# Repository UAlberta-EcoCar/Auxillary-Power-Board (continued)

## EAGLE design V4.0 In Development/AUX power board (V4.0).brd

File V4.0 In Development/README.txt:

Changes From V3

Completed:
	SEPTIC 12V 1.25A Surface Mount Regulator w/ Vin 8-18V, 90% efficiency

	Surface Mount 328p

	A -12V low current regulator for operation of op-amps.

	Surface Mount 5V 1.25A (it does 2A) buck convertor. 

	Using a cheaper inductor for the 5V regulator

	Using low side nMOS for reverse polarity protection

	Only have 2 outputs. One to FCC board (if needed) and to Aux Board. Still keep 
	a header for testing.

	I inverted the RJ11 Port

	Implemented Overvoltage protection
	
	Implemented reverse voltage protection
	
	Add a standardized fuse holder

Planned:
	i2c 0.96" 128x64 display (Possibly a no to data logging, favoring real-time power measurements)

	Use existing Heat Sink and place on the bottom of the board

	Add holes to the outside of the board (ease of mounting)

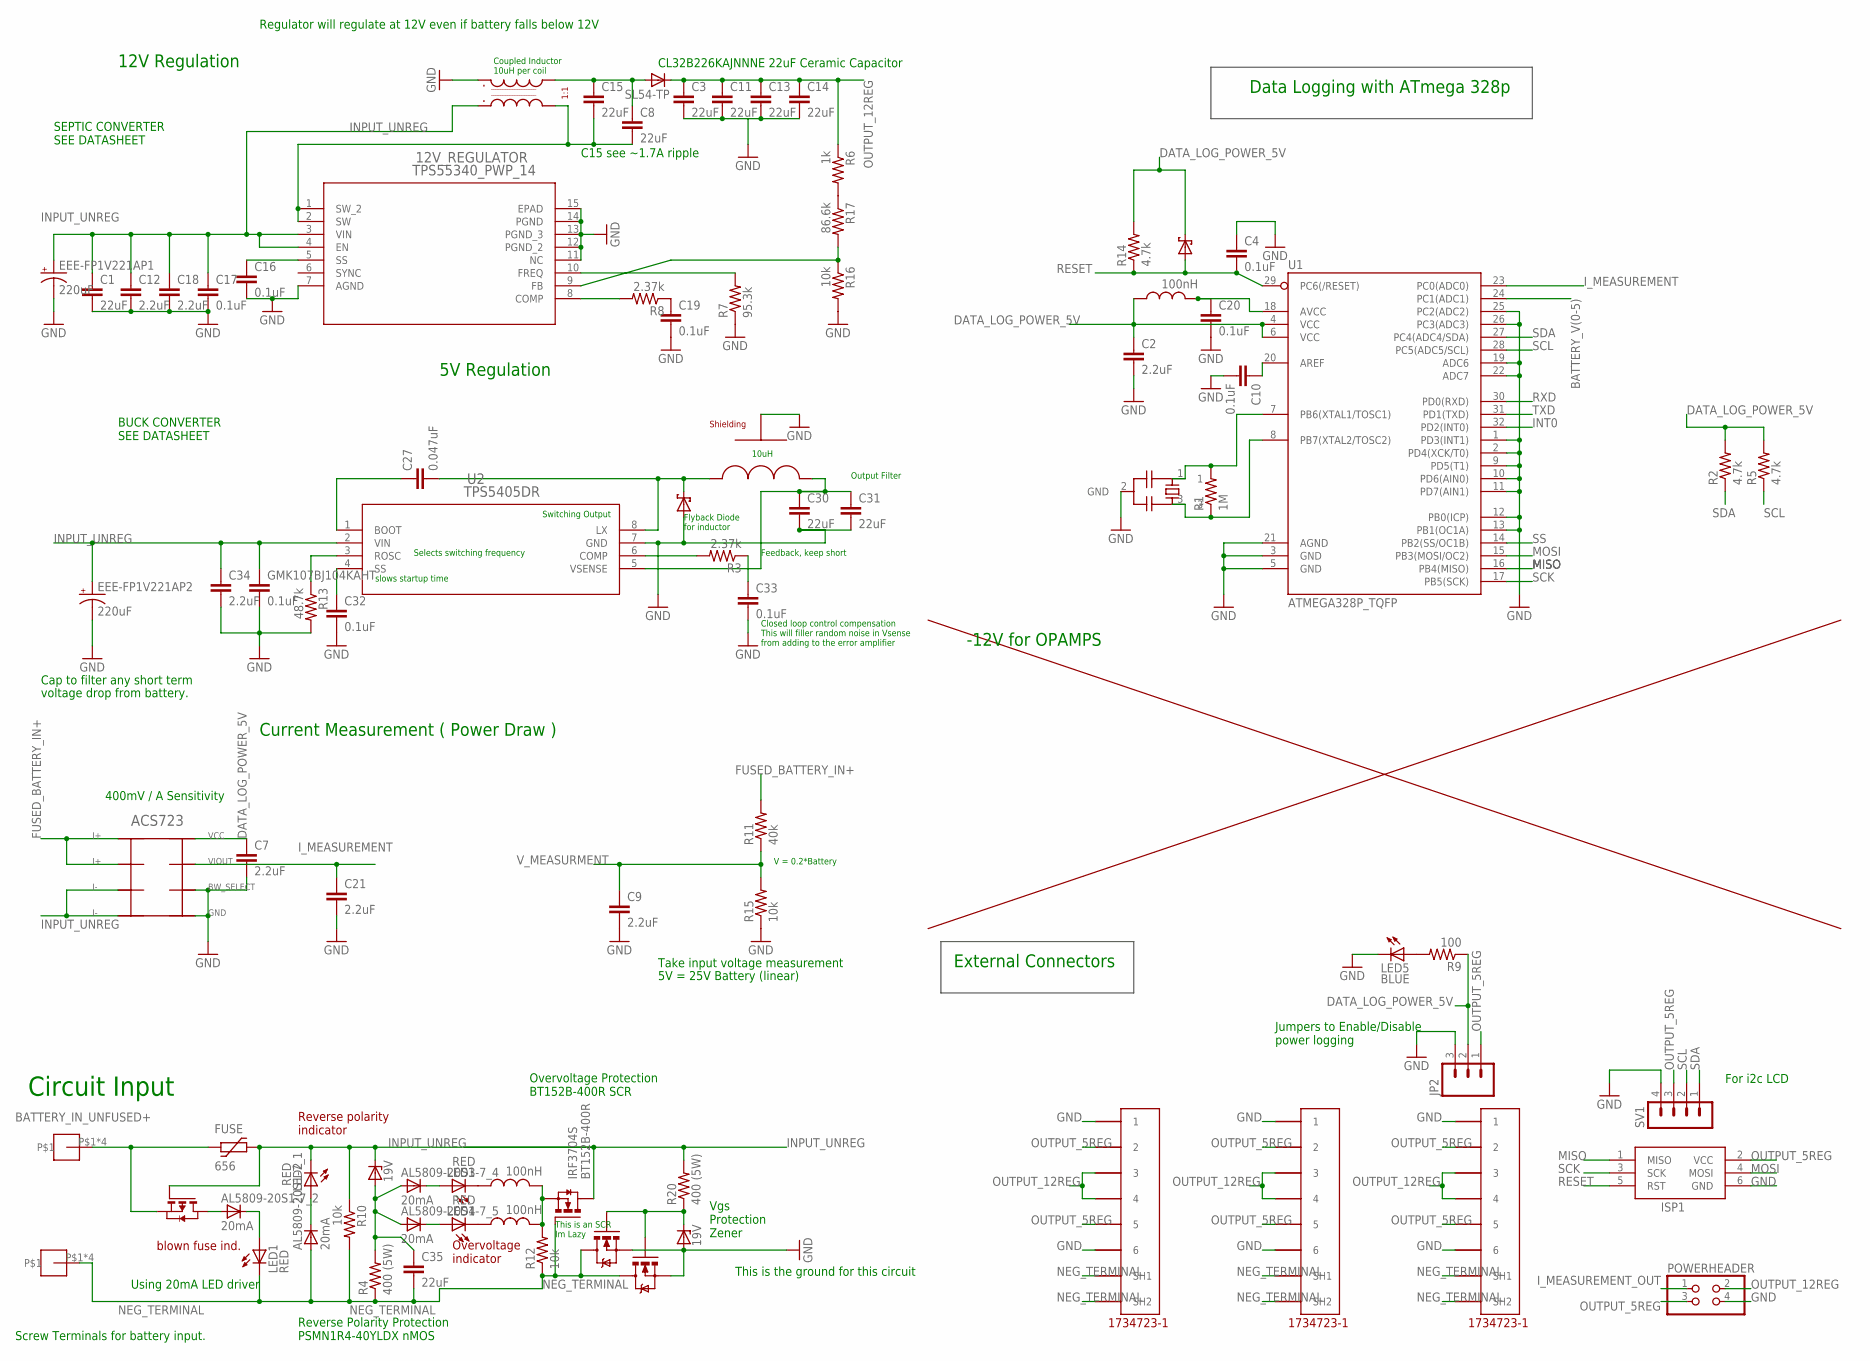
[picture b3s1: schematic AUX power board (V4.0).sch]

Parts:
1N5354BRLG, 1N5356BRLG_1: 19V; DO41Z10
12V_REGULATOR: TPS55340_PWP_14; PWP14
16MHZ: CSTCE16M0V53-R0; RESONATOR
AL5809-20S1-7_1, AL5809-20S1-7_2, AL5809-20S1-7_4, AL5809-20S1-7_5: 20mA; SOD123
BT152B-400R: IRF3704S; D2PACK
C1, C3, C8, C11, C13, C14, C15, C30, C31, C35: 22uF; C1210
C2, C7, C9, C12, C18, C21, C34: 2.2uF; C0603
C4, C10, C16, C17, C19, C20, C32, C33: 0.1uF; C0603
C27: 0.047uF; C0603
EEE-FP1V221AP1, EEE-FP1V221AP2: 220uF; 175TMP-0808
FUSE: 656
GMK107BJ104KAHT: 0.1uF; C0603
ISP1: AVRISP-6; AVRISP
JP2: M03PTH; 1X03
LED1, LED2, LED3, LED4: RED; SML1206
LED5: BLUE; SML1206
MLZ2012DR10DT000, MLZ2012DR10DT001, MLZ2012DR10DT002: 100nH; L2012C
MURS120T3G, MURS120T3G1: MBRS130LT3; SMB
POWERHEADER: PINHD-2X2; 2X02
PSMN1R4-40YLDX1, PSMN1R4-40YLDX2: MOSFET-NCHANNELFDS6630A; POWERSO08
R1: 1M; R0603
R2, R5, R14: 4.7k; R0805
R3, R8: 2.37k; R0603
R4, R20: 400 (5W); P0817/22
R6: 1k; R0805
R7: 95.3k; R0603
R9: 100; R0805
R10, R12, R15, R16: 10k; R0805
R11: 40k; R0805
R13: 48.7k; R0805
R17: 86.6k; R0805
SL54-TP: DIODE_E-SMC; DIODE_SMC
SV1: MA04-1
U1: ATMEGA328P_TQFP; TQFP32-08
U2: TPS5405DR; D8
U$1: ACS723; SO08
U$3, U$4, U$10: 5555140-6; 1734723-1_RJ11
U$5: CDEP147NP-100MC-125; NONSTANDARD
U$6, U$7: SCREW-8191
U$9: 744873100; 1592
ZVP4525E6TA_1: MOSFET-PCHANNELFDS6675; SOT23-6

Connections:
BATTERY_IN_UNFUSED+: FUSE.P$1 (1), U$6.P$1, U$6.P$2, U$6.P$3, U$6.P$4, ZVP4525E6TA_1.4 (S)
BATTERY_V(0-5): U1.24 (PC1(ADC1))
DATA_LOG_POWER_5V: C2.1, C7.1, JP2.2, MLZ2012DR10DT000.1, MURS120T3G1.C, R2.2, R5.2, R9.1, R14.2, U1.4 (VCC), U1.6 (VCC), U$1.8
FUSED_BATTERY_IN+: R11.2, U$1.1, U$1.2
GND: 1N5356BRLG_1.A, 12V_REGULATOR.7 (AGND), 12V_REGULATOR.11 (NC), 12V_REGULATOR.12 (PGND_2), 12V_REGULATOR.13 (PGND_3), 12V_REGULATOR.14 (PGND), 12V_REGULATOR.15 (EPAD), 16MHZ.2 (GND), C1.2, C2.2, C3.2, C4.1, C7.2, C9.2, C10.2, C11.2, C12.2, C13.2, C14.2, C16.2, C17.2, C18.2, C19.2, C20.2, C21.2, C30.2, C31.2, C32.2, C33.2, C34.2, EEE-FP1V221AP1.-, EEE-FP1V221AP2.-, GMK107BJ104KAHT.2, ISP1.6 (GND), JP2.3, LED5.C, MURS120T3G.A, POWERHEADER.4, PSMN1R4-40YLDX1.SOURCE (S), PSMN1R4-40YLDX1.SOURCE1 (S), PSMN1R4-40YLDX1.SOURCE2 (S), PSMN1R4-40YLDX2.SOURCE (S), PSMN1R4-40YLDX2.SOURCE1 (S), PSMN1R4-40YLDX2.SOURCE2 (S), R7.1, R13.2, R15.1, R16.2, SV1.4, U1.1 (PD3(INT1)), U1.2 (PD4(XCK/T0)), U1.3 (GND), U1.5 (GND), U1.9 (PD5(T1)), U1.10 (PD6(AIN0)), U1.11 (PD7(AIN1)), U1.12 (PB0(ICP)), U1.13 (PB1(OC1A)), U1.19 (ADC6), U1.21 (AGND), U1.22 (ADC7), U1.25 (PC2(ADC2)), U1.26 (PC3(ADC3)), U2.7 (GND), U$1.5, U$1.6, U$3.6, U$4.6, U$5.GND, U$9.L1_P1 (L1_A), U$10.6
INPUT_UNREG: 1N5354BRLG.C, 12V_REGULATOR.3 (VIN), 12V_REGULATOR.4 (EN), BT152B-400R.2 (D), C1.1, C12.1, C17.1, C18.1, C34.1, EEE-FP1V221AP1.+, EEE-FP1V221AP2.+, FUSE.P$2 (2), GMK107BJ104KAHT.1, LED2.C, R10.1, R20.2, U2.2 (VIN), U$1.3, U$1.4, U$9.L2_P2 (L2_A), ZVP4525E6TA_1.3 (G)
INT0: U1.32 (PD2(INT0))
I_MEASUREMENT: C21.1, U1.23 (PC0(ADC0)), U$1.7
I_MEASUREMENT_OUT: POWERHEADER.1
MISO: ISP1.1 (MISO), U1.16 (PB4(MISO))
MOSI: ISP1.4 (MOSI), U1.15 (PB3(MOSI/OC2))
unnamed: C27.1, U2.1 (BOOT)
unnamed: R6.2, R17.1
unnamed: 12V_REGULATOR.1 (SW_2), 12V_REGULATOR.2 (SW), C8.2, C15.2, U$9.L2_P3 (L2_B)
unnamed: C20.1, MLZ2012DR10DT000.2, U1.18 (AVCC)
unnamed: C8.1, C15.1, SL54-TP.A (C), U$9.L1_P4 (L1_B)
unnamed: C27.2, MURS120T3G.C, U2.8 (LX), U$5.PAD1 (PIN1)
unnamed: 12V_REGULATOR.5 (SS), C16.1
unnamed: 12V_REGULATOR.8 (COMP), R8.2
unnamed: 12V_REGULATOR.10 (FREQ), R7.2
unnamed: C19.1, R8.1
unnamed: C10.1, U1.20 (AREF)
unnamed: 12V_REGULATOR.9 (FB), R16.1, R17.2
unnamed: AL5809-20S1-7_2.2 (A), ZVP4525E6TA_1.1 (D), ZVP4525E6TA_1.2 (D), ZVP4525E6TA_1.5 (D), ZVP4525E6TA_1.6 (D)
unnamed: 16MHZ.1, R1.2, U1.7 (PB6(XTAL1/TOSC1))
unnamed: 1N5356BRLG_1.C, PSMN1R4-40YLDX1.GATE (G), PSMN1R4-40YLDX2.GATE (G), R20.1
unnamed: R13.1, U2.3 (ROSC)
unnamed: C32.1, U2.4 (SS)
unnamed: AL5809-20S1-7_1.1 (C), LED2.A
unnamed: C33.1, R3.1
unnamed: R3.2, U2.6 (COMP)
unnamed: AL5809-20S1-7_2.1 (C), LED1.A
unnamed: C30.1, C31.1, U2.5 (VSENSE), U$5.PAD2 (PIN2)
unnamed: 16MHZ.3, R1.1, U1.8 (PB7(XTAL2/TOSC2))
unnamed: AL5809-20S1-7_4.1 (C), LED3.A
unnamed: 1N5354BRLG.A, AL5809-20S1-7_4.2 (A), AL5809-20S1-7_5.2 (A), C35.1, R4.2
unnamed: LED3.C, MLZ2012DR10DT001.1
unnamed: AL5809-20S1-7_5.1 (C), LED4.A
unnamed: LED4.C, MLZ2012DR10DT002.1
unnamed: BT152B-400R.3 (S), MLZ2012DR10DT001.2, MLZ2012DR10DT002.2, R12.2
unnamed: LED5.A, R9.2
NEG_TERMINAL: AL5809-20S1-7_1.2 (A), BT152B-400R.1 (G), C35.2, LED1.C, PSMN1R4-40YLDX1.DRAIN (D), PSMN1R4-40YLDX1.DRAIN1 (D), PSMN1R4-40YLDX2.DRAIN (D), PSMN1R4-40YLDX2.DRAIN1 (D), R4.1, R10.2, R12.1, U$3.SH1, U$3.SH2, U$4.SH1, U$4.SH2, U$7.P$1, U$7.P$2, U$7.P$3, U$7.P$4, U$10.SH1, U$10.SH2
OUTPUT_5REG: ISP1.2 (VCC), JP2.1, POWERHEADER.3, SV1.3, U$3.2, U$3.5, U$4.2, U$4.5, U$10.2, U$10.5
OUTPUT_12REG: C3.1, C11.1, C13.1, C14.1, POWERHEADER.2, R6.1, SL54-TP.C (A), U$3.3, U$3.4, U$4.3, U$4.4, U$10.3, U$10.4
RESET: C4.2, ISP1.5 (RST), MURS120T3G1.A, R14.1, U1.29 (PC6(/RESET))
RXD: U1.30 (PD0(RXD))
SCK: ISP1.3 (SCK), U1.17 (PB5(SCK))
SCL: R5.1, SV1.2, U1.28 (PC5(ADC5/SCL))
SDA: R2.1, SV1.1, U1.27 (PC4(ADC4/SDA))
SS: U1.14 (PB2(SS/OC1B))
TXD: U1.31 (PD1(TXD))
V_MEASURMENT: C9.1, R11.1, R15.2

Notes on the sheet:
12V Regulation
5V Regulation
Current Measurement ( Power Draw )
Circuit Input
Data Logging with ATmega 328p
External Connectors
Jumpers to Enable/Disable power logging
Screw Terminals for battery input.
Cap to filter any short term
voltage drop from battery.
Take input voltage measurement
5V = 25V Battery (linear)
V = 0.2*Battery
Regulator will regulate at 12V even if battery falls below 12V
CL32B226KAJNNNE 22uF Ceramic Capacitor
-12V for OPAMPS
C15 see ~1.7A ripple
400mV / A Sensitivity
SEPTIC CONVERTER SEE DATASHEET
BUCK CONVERTER SEE DATASHEET
slows startup time
Selects switching frequency
Closed loop control compensation This will filler random noise in Vsense from adding to the error amplifier
Feedback, keep short
Output Filter
Flyback Diode for inductor
Switching Output
Coupled Inductor 10uH per coil
10uH
Overvoltage Protection BT152B-400R SCR
blown fuse ind.
Reverse polarity indicator
Reverse Polarity Protection PSMN1R4-40YLDX nMOS
For i2c LCD
Using 20mA LED driver
This is an SCR Im Lazy
This is the ground for this circuit
Vgs Protection Zener
Overvoltage indicator

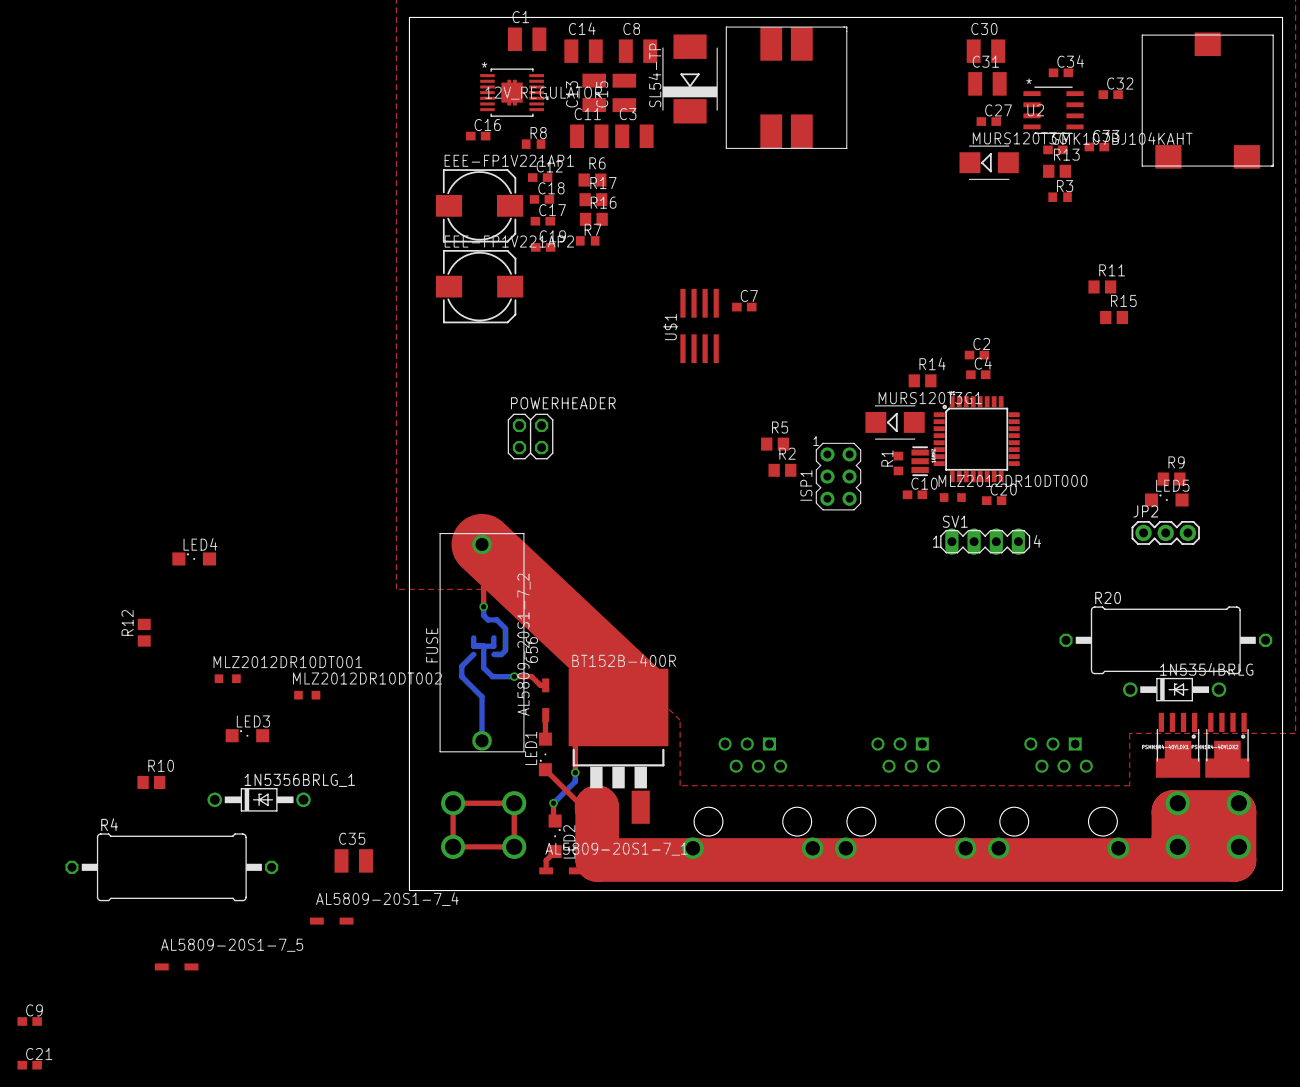
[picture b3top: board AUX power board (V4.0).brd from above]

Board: 2 copper layers, 100.0 x 100.0 mm, 85 parts (1 on the bottom side), 46 nets.

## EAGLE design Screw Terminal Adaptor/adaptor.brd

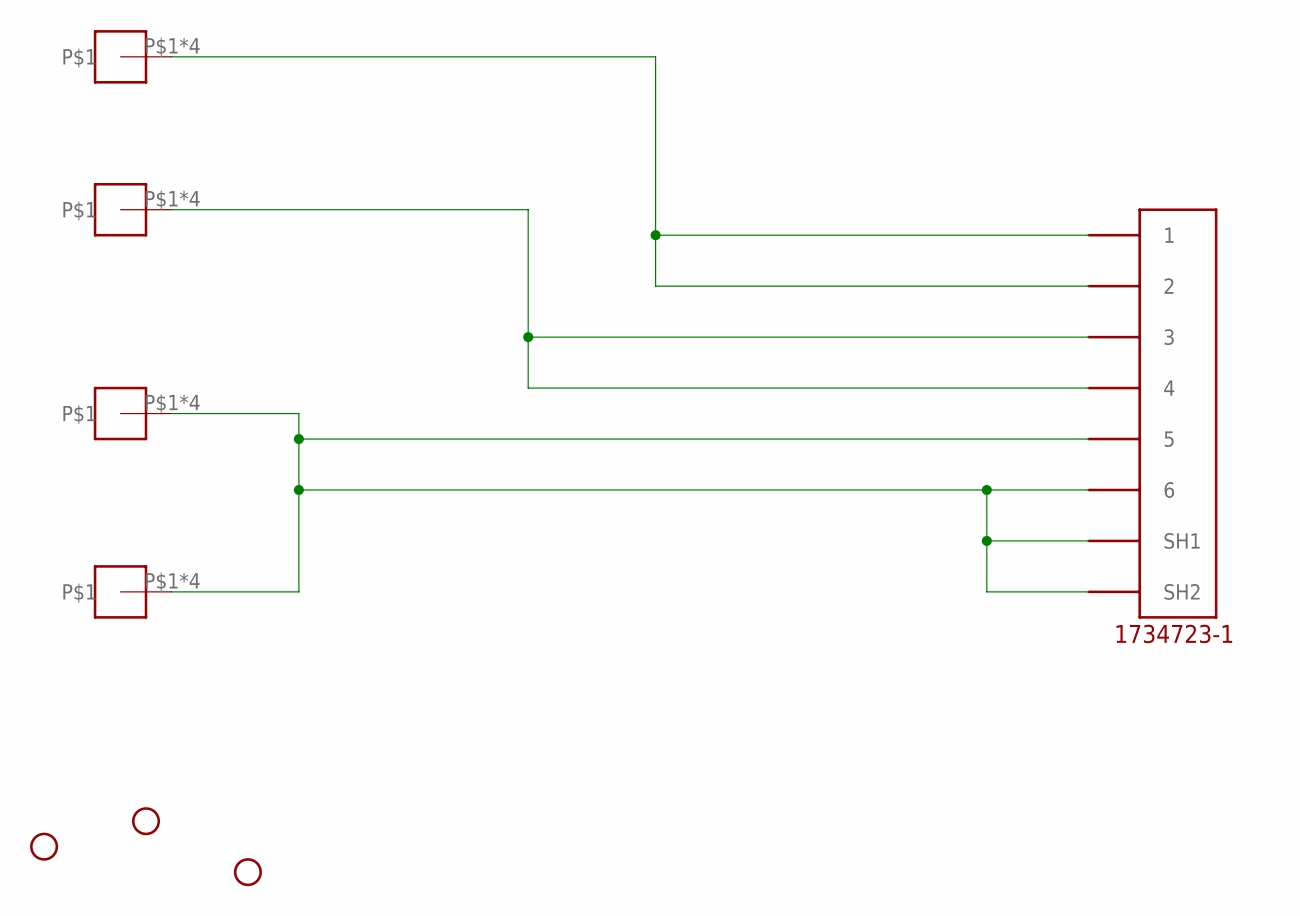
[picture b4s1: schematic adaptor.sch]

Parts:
H1, H2, H3: STAND-OFF
U$1, U$2, U$4, U$6: SCREW-8191
U$3: 5555140-6; 1734723-1_RJ11

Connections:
5V: U$1.P$1, U$1.P$2, U$1.P$3, U$1.P$4, U$3.3, U$3.4
12V: U$3.1, U$3.2, U$6.P$1, U$6.P$2, U$6.P$3, U$6.P$4
GND: U$2.P$1, U$2.P$2, U$2.P$3, U$2.P$4, U$3.5, U$3.6, U$3.SH1, U$3.SH2, U$4.P$1, U$4.P$2, U$4.P$3, U$4.P$4

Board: 2 copper layers, 8 parts (0 on the bottom side), 3 nets, no tracks yet.

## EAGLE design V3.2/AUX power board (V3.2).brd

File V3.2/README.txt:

Did some reading on reverse current protection and found the diode short between
+ and gnd might not be good enough since it takes a bit to blow the fuse. 
Also its annoying that the fuse blows. 

Solution was to place a well selected pMOS in its place. I selected the FDS6681Z,
and placed 2 of them in parallel in place of the diode. 

The Rds on is 4.5mohm so 2 of them would have 2.25mohm. This results in a power loss 
of (2.25A max) about 15mW. But we wont be using 2.25A, a realistic current is about 
1A. so thats around 2.5mW.

-Koltin Kosik-Harvey

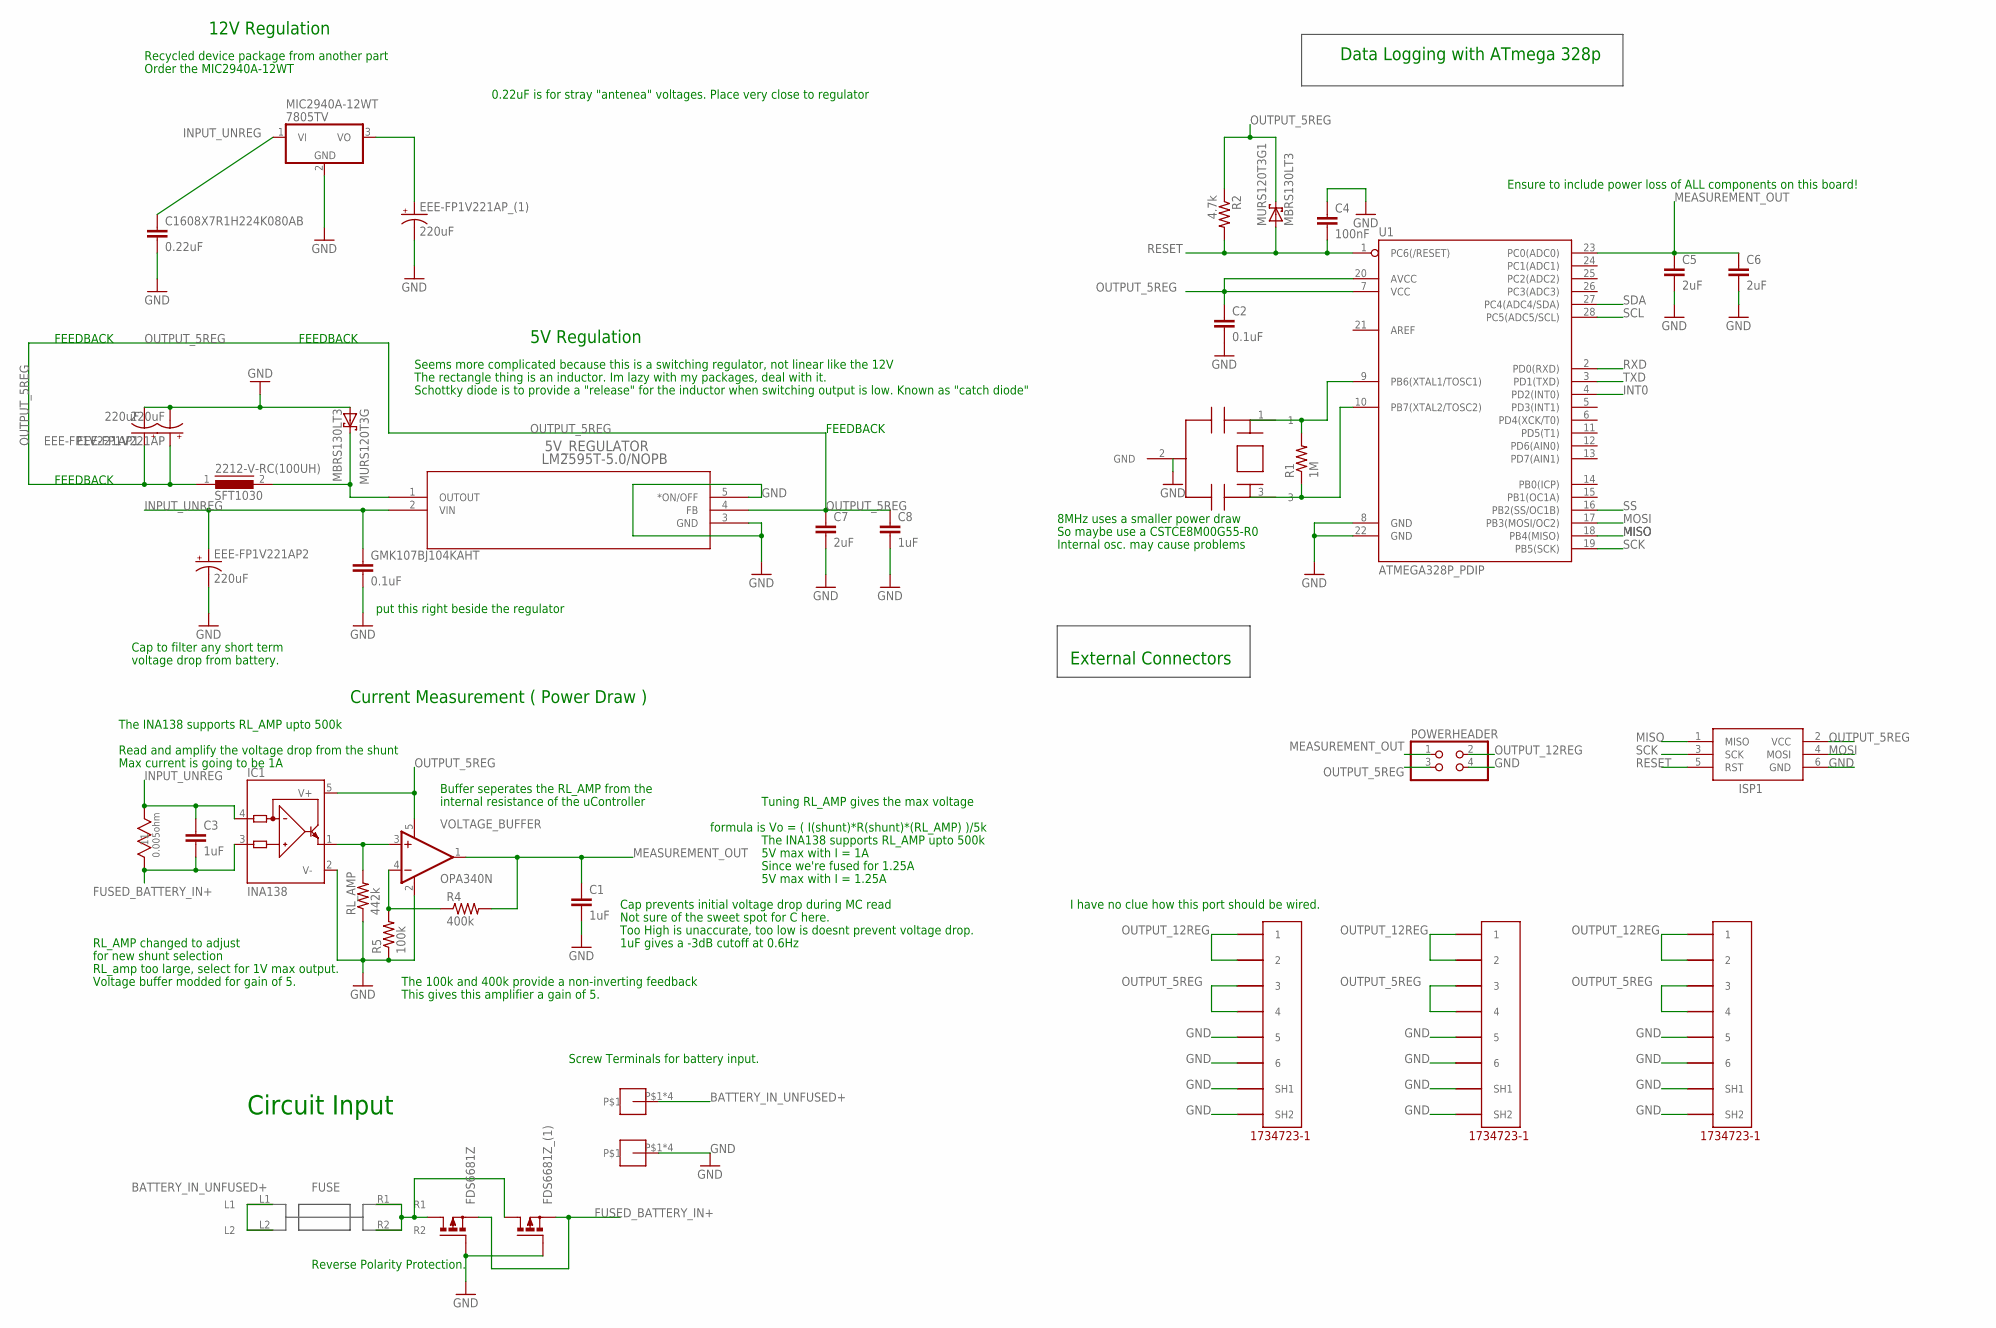
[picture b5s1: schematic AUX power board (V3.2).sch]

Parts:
5V_REGULATOR: LM2595T-5.0/NOPB; T05D
15FR005E: 15FR005E; RES_15
2212-V-RC(100UH): SFT1030
C1, C3, C8: 1uF; C0603
C2: 0.1uF; C0603
C4: 100nF; C0603
C5, C6, C7: 2uF; C0603
C1608X7R1H224K080AB: 0.22uF; C0603
CSTCE8M00G55-R0: CSTCE16M0V53-R0; RESONATOR
EEE-FP1V221AP, EEE-FP1V221AP1, EEE-FP1V221AP2, EEE-FP1V221AP_(1): 220uF; 175TMP-0808
FDS6681Z, FDS6681Z_(1): P-MOSFET-SO8; SO-08
GMK107BJ104KAHT: 0.1uF; C0603
IC1: INA138; SOT23-5
ISP1: AVRISP-6; AVRISP
MIC2940A-12WT: 7805TV; TO220V
MINIBLADE: 3568
MURS120T3G, MURS120T3G1: MBRS130LT3; SMB
POWERHEADER: PINHD-2X2; 2X02
R1: 1M; R0603
R2: 4.7k; R0603
R4: 400k; R0603
R5: 100k; R0603
RL_AMP: 442k; R0603
U1: ATMEGA328P_PDIP; DIL28-3
U$3, U$4, U$5: 5555140-6; 1734723-1_RJ11
U$6, U$7: SCREW-8191
VOLTAGE_BUFFER: OPA340N; SOT23-5

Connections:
BATTERY_IN_UNFUSED+: MINIBLADE.L1, MINIBLADE.L2, U$6.P$1, U$6.P$2, U$6.P$3, U$6.P$4
FUSED_BATTERY_IN+: 15FR005E.1 (11), C3.2, FDS6681Z.1 (S), FDS6681Z.2 (S), FDS6681Z.3 (S), FDS6681Z_(1).1 (S), FDS6681Z_(1).2 (S), FDS6681Z_(1).3 (S), IC1.3 (IN+)
GND: 5V_REGULATOR.3 (GND), 5V_REGULATOR.5 (*ON/OFF), C1.2, C2.2, C4.1, C5.2, C6.2, C7.2, C8.2, C1608X7R1H224K080AB.2, CSTCE8M00G55-R0.2 (GND), EEE-FP1V221AP.-, EEE-FP1V221AP1.-, EEE-FP1V221AP2.-, EEE-FP1V221AP_(1).-, FDS6681Z.4 (G), FDS6681Z_(1).4 (G), GMK107BJ104KAHT.2, IC1.2 (V-), ISP1.6 (GND), MIC2940A-12WT.2 (GND), MURS120T3G.A, POWERHEADER.4, R5.1, RL_AMP.1, U1.8 (GND), U1.22 (GND), U$3.5, U$3.6, U$3.SH1, U$3.SH2, U$4.5, U$4.6, U$4.SH1, U$4.SH2, U$5.5, U$5.6, U$5.SH1, U$5.SH2, U$7.P$1, U$7.P$2, U$7.P$3, U$7.P$4, VOLTAGE_BUFFER.2 (V-)
INPUT_UNREG: 5V_REGULATOR.2 (VIN), 15FR005E.2 (22), C3.1, C1608X7R1H224K080AB.1, EEE-FP1V221AP2.+, GMK107BJ104KAHT.1, IC1.4 (IN-), MIC2940A-12WT.1 (VI)
INT0: U1.4 (PD2(INT0))
MEASUREMENT_OUT: C1.1, C5.1, C6.1, POWERHEADER.1, R4.2, U1.23 (PC0(ADC0)), VOLTAGE_BUFFER.1 (OUT)
MISO: ISP1.1 (MISO), U1.18 (PB4(MISO))
MMM: FDS6681Z.5 (D), FDS6681Z.6 (D), FDS6681Z.7 (D), FDS6681Z.8 (D), FDS6681Z_(1).5 (D), FDS6681Z_(1).6 (D), FDS6681Z_(1).7 (D), FDS6681Z_(1).8 (D), MINIBLADE.R1, MINIBLADE.R2
MOSI: ISP1.4 (MOSI), U1.17 (PB3(MOSI/OC2))
unnamed: 5V_REGULATOR.1 (OUTOUT), 2212-V-RC(100UH).2, MURS120T3G.C
unnamed: R4.1, R5.2, VOLTAGE_BUFFER.4 (-IN)
unnamed: IC1.1 (OUT), RL_AMP.2, VOLTAGE_BUFFER.3 (+IN)
unnamed: CSTCE8M00G55-R0.1, R1.2, U1.9 (PB6(XTAL1/TOSC1))
unnamed: CSTCE8M00G55-R0.3, R1.1, U1.10 (PB7(XTAL2/TOSC2))
OUTPUT_5REG: 5V_REGULATOR.4 (FB), 2212-V-RC(100UH).1, C2.1, C7.1, C8.1, EEE-FP1V221AP.+, EEE-FP1V221AP1.+, IC1.5 (V+), ISP1.2 (VCC), MURS120T3G1.C, POWERHEADER.3, R2.1, U1.7 (VCC), U1.20 (AVCC), U$3.3, U$3.4, U$4.3, U$4.4, U$5.3, U$5.4, VOLTAGE_BUFFER.5 (V+)
OUTPUT_12REG: EEE-FP1V221AP_(1).+, MIC2940A-12WT.3 (VO), POWERHEADER.2, U$3.1, U$3.2, U$4.1, U$4.2, U$5.1, U$5.2
RESET: C4.2, ISP1.5 (RST), MURS120T3G1.A, R2.2, U1.1 (PC6(/RESET))
RXD: U1.2 (PD0(RXD))
SCK: ISP1.3 (SCK), U1.19 (PB5(SCK))
SCL: U1.28 (PC5(ADC5/SCL))
SDA: U1.27 (PC4(ADC4/SDA))
SS: U1.16 (PB2(SS/OC1B))
TXD: U1.3 (PD1(TXD))

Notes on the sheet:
12V Regulation
Recycled device package from another part
5V Regulation
Seems more complicated because this is a switching regulator, not linear like the 12V
0.22uF is for stray "antenea" voltages. Place very close to regulator
Schottky diode is to provide a "release" for the inductor when switching output is low. Known as "catch diode"
The rectangle thing is an inductor. Im lazy with my packages, deal with it.
FEEDBACK
put this right beside the regulator
Current Measurement ( Power Draw )
Cap prevents initial voltage drop during MC read
Buffer seperates the RL_AMP from the
internal resistance of the uController
Read and amplify the voltage drop from the shunt
Tuning RL_AMP gives the max voltage
formula is Vo = ( I(shunt)*R(shunt)*(RL_AMP) )/5k
The INA138 supports RL_AMP upto 500k
Not sure of the sweet spot for C here.
Too High is unaccurate, too low is doesnt prevent voltage drop.
1uF gives a -3dB cutoff at 0.6Hz
Circuit Input
Data Logging with ATmega 328p
External Connectors
I have no clue how this port should be wired.
So maybe use a CSTCE8M00G55-R0
8MHz uses a smaller power draw
Internal osc. may cause problems
5V max with I = 1A
Max current is going to be 1A
Since we're fused for 1.25A
5V max with I = 1.25A
Ensure to include power loss of ALL components on this board!
Screw Terminals for battery input.
Order the MIC2940A-12WT
Reverse Polarity Protection.
Cap to filter any short term
voltage drop from battery.
The 100k and 400k provide a non-inverting feedback
This gives this amplifier a gain of 5.
RL_AMP changed to adjust

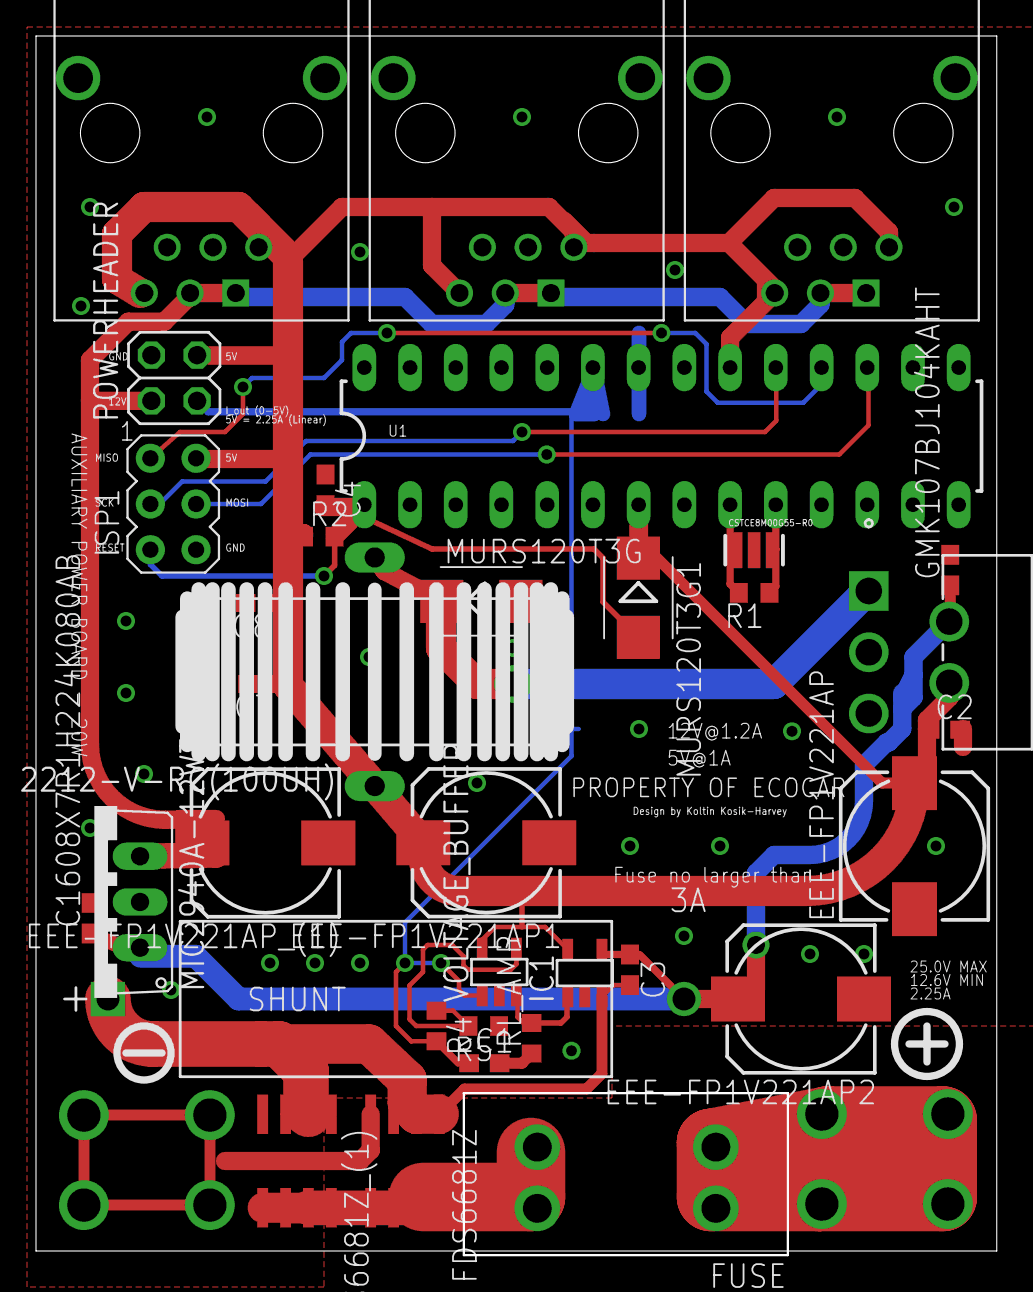
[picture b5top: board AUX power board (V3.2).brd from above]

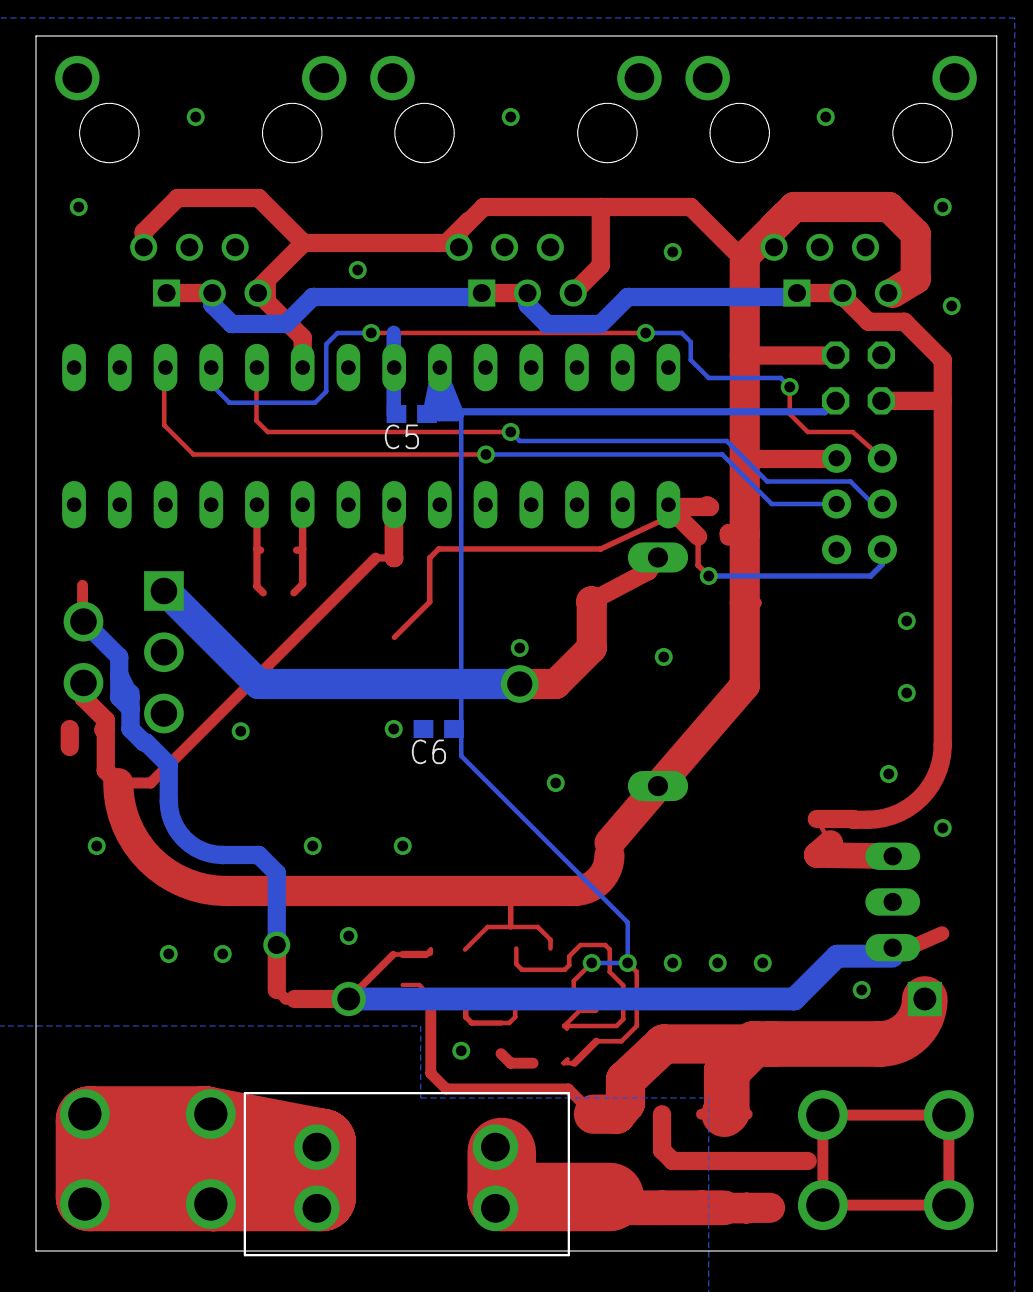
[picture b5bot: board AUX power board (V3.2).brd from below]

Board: 2 copper layers, 53.4 x 67.5 mm, 39 parts (2 on the bottom side), 17 nets.

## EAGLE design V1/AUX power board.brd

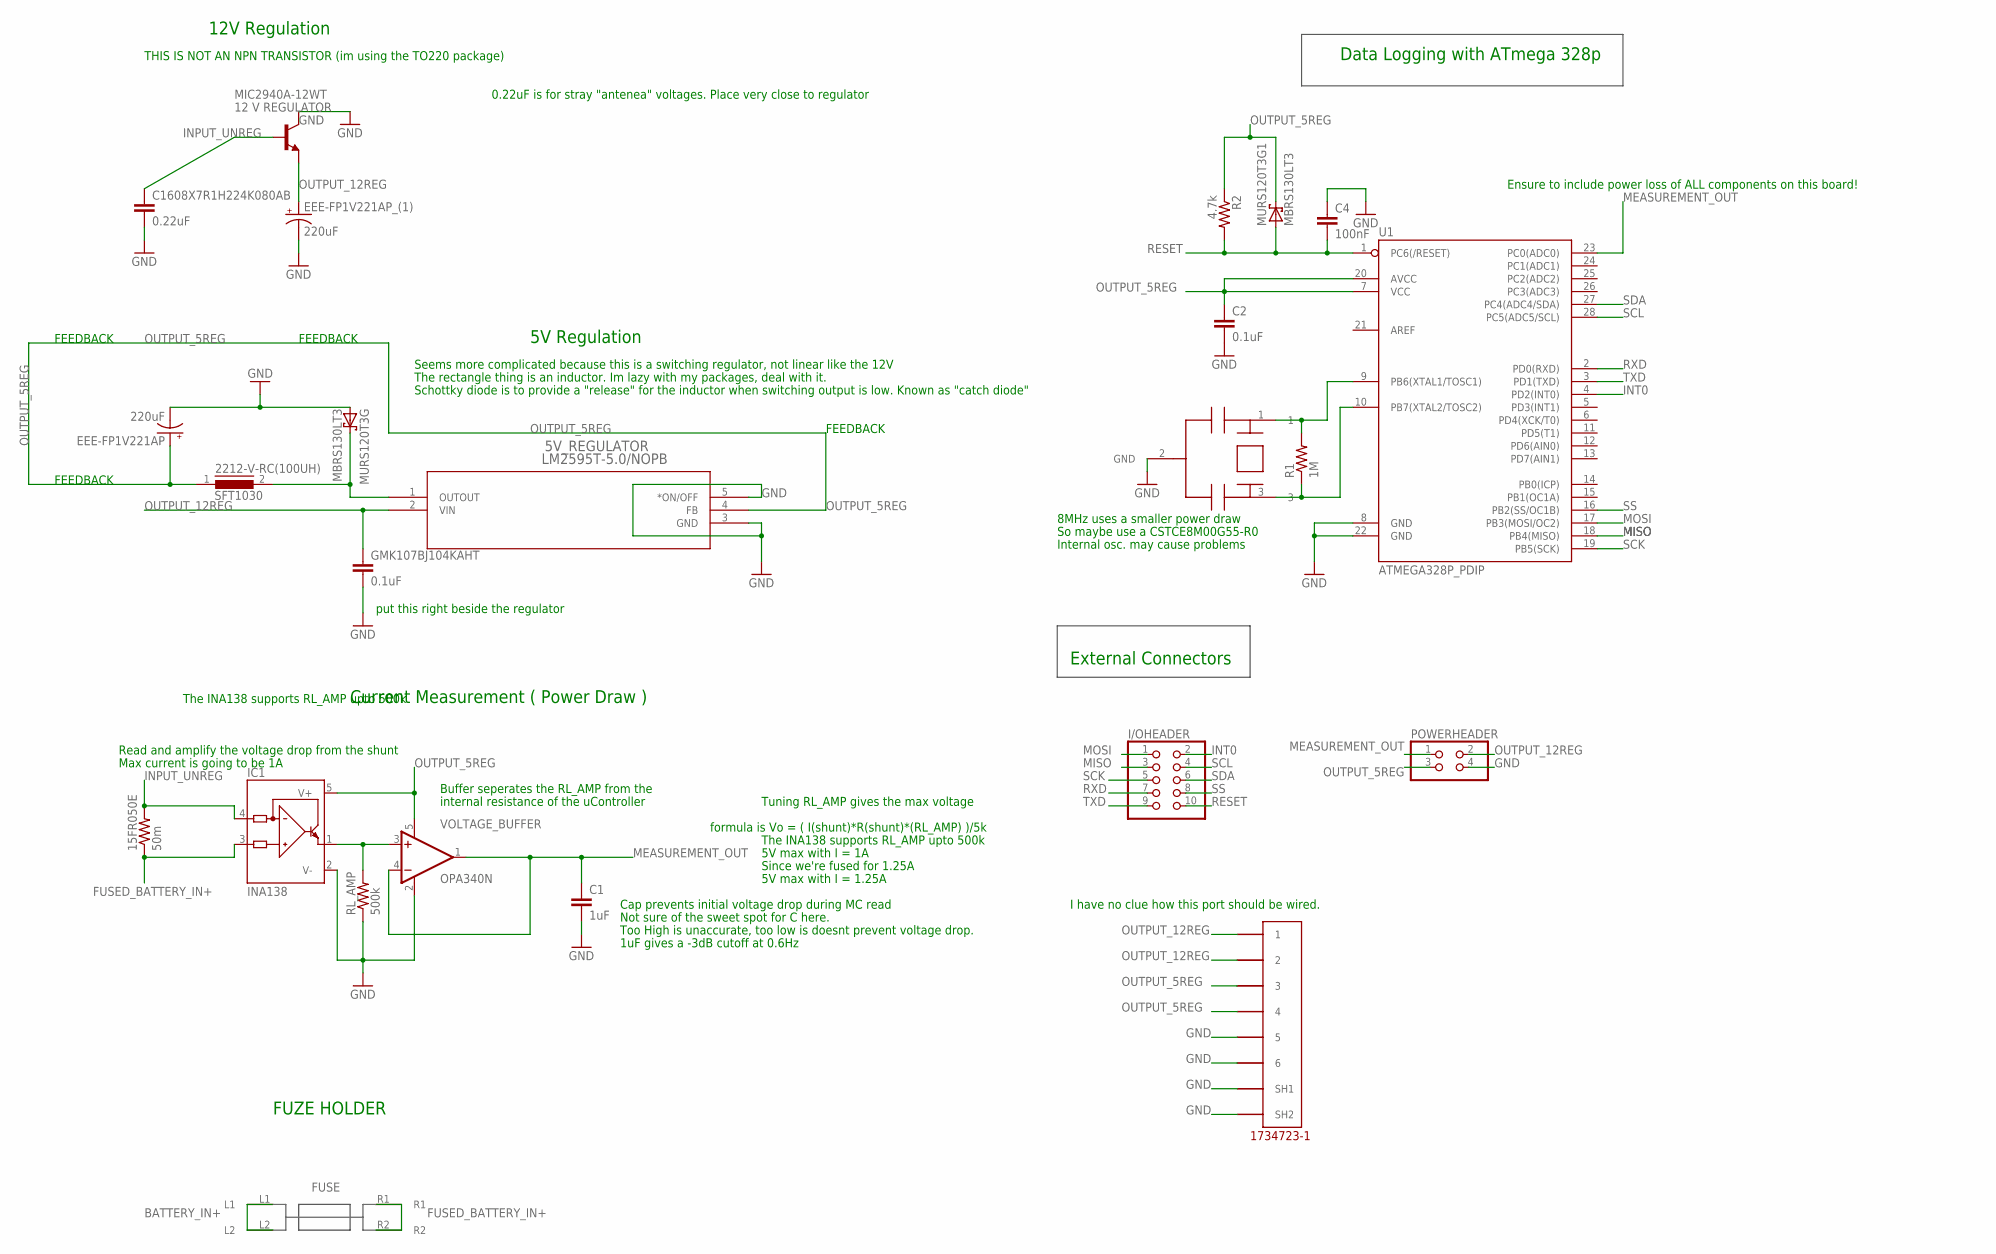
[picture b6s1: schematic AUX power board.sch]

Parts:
5V_REGULATOR: LM2595T-5.0/NOPB; T05D
15FR050E: 50m; 0617/22
2212-V-RC(100UH): SFT1030
C1: 1uF; C0603
C2: 0.1uF; C0603
C4: 100nF; C0603
C1608X7R1H224K080AB: 0.22uF; C0603
EEE-FP1V221AP, EEE-FP1V221AP_(1): 220uF; 175TMP-0808
GMK107BJ104KAHT: 0.1uF; C0603
I/OHEADER: PINHD-2X5; 2X05
IC1: INA138; SOT23-5
MIC2940A-12WT: 12 V REGULATOR; TO220
MINIBLADE: 3568
MURS120T3G, MURS120T3G1: MBRS130LT3; SMB
POWERHEADER: PINHD-2X2; 2X02
R1: 1M; R0603
R2: 4.7k; R0603
RL_AMP: 500k; R0603
U1: ATMEGA328P_PDIP; DIL28-3
U$1: CSTCE16M0V53-R0; RESONATOR
U$3: 5555140-6; 1734723-1_RJ11
VOLTAGE_BUFFER: OPA340N; SOT23-5

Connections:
BATTERY_IN+: MINIBLADE.L1, MINIBLADE.L2
FUSED_BATTERY_IN+: 15FR050E.1, IC1.3 (IN+), MINIBLADE.R1, MINIBLADE.R2
GND: 5V_REGULATOR.3 (GND), 5V_REGULATOR.5 (*ON/OFF), C1.2, C2.2, C4.1, C1608X7R1H224K080AB.2, EEE-FP1V221AP.-, EEE-FP1V221AP_(1).-, GMK107BJ104KAHT.2, IC1.2 (V-), MIC2940A-12WT.2 (C), MURS120T3G.A, POWERHEADER.4, RL_AMP.1, U1.8 (GND), U1.22 (GND), U$3.5, U$3.6, U$3.SH1, U$3.SH2, VOLTAGE_BUFFER.2 (V-)
INPUT_UNREG: 15FR050E.2, C1608X7R1H224K080AB.1, IC1.4 (IN-), MIC2940A-12WT.1 (B)
INT0: I/OHEADER.2, U1.4 (PD2(INT0))
MEASUREMENT_OUT: C1.1, POWERHEADER.1, U1.23 (PC0(ADC0)), VOLTAGE_BUFFER.1 (OUT), VOLTAGE_BUFFER.4 (-IN)
MISO: I/OHEADER.3, U1.18 (PB4(MISO))
MOSI: I/OHEADER.1, U1.17 (PB3(MOSI/OC2))
unnamed: 5V_REGULATOR.1 (OUTOUT), 2212-V-RC(100UH).2, MURS120T3G.C
unnamed: IC1.1 (OUT), RL_AMP.2, VOLTAGE_BUFFER.3 (+IN)
unnamed: R1.2, U1.9 (PB6(XTAL1/TOSC1))
unnamed: R1.1, U1.10 (PB7(XTAL2/TOSC2))
OUTPUT_5REG: 5V_REGULATOR.4 (FB), 2212-V-RC(100UH).1, C2.1, EEE-FP1V221AP.+, IC1.5 (V+), MURS120T3G1.C, POWERHEADER.3, R2.1, U1.7 (VCC), U1.20 (AVCC), U$3.3, U$3.4, VOLTAGE_BUFFER.5 (V+)
OUTPUT_12REG: 5V_REGULATOR.2 (VIN), EEE-FP1V221AP_(1).+, GMK107BJ104KAHT.1, MIC2940A-12WT.3 (E), POWERHEADER.2, U$3.1, U$3.2
RESET: C4.2, I/OHEADER.10, MURS120T3G1.A, R2.2, U1.1 (PC6(/RESET))
RXD: I/OHEADER.7, U1.2 (PD0(RXD))
SCK: I/OHEADER.5, U1.19 (PB5(SCK))
SCL: I/OHEADER.4, U1.28 (PC5(ADC5/SCL))
SDA: I/OHEADER.6, U1.27 (PC4(ADC4/SDA))
SS: I/OHEADER.8, U1.16 (PB2(SS/OC1B))
TXD: I/OHEADER.9, U1.3 (PD1(TXD))

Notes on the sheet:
12V Regulation
THIS IS NOT AN NPN TRANSISTOR (im using the TO220 package)
5V Regulation
Seems more complicated because this is a switching regulator, not linear like the 12V
0.22uF is for stray "antenea" voltages. Place very close to regulator
Schottky diode is to provide a "release" for the inductor when switching output is low. Known as "catch diode"
The rectangle thing is an inductor. Im lazy with my packages, deal with it.
FEEDBACK
put this right beside the regulator
Current Measurement ( Power Draw )
Cap prevents initial voltage drop during MC read
Buffer seperates the RL_AMP from the
internal resistance of the uController
Read and amplify the voltage drop from the shunt
Tuning RL_AMP gives the max voltage
formula is Vo = ( I(shunt)*R(shunt)*(RL_AMP) )/5k
The INA138 supports RL_AMP upto 500k
Not sure of the sweet spot for C here.
Too High is unaccurate, too low is doesnt prevent voltage drop.
1uF gives a -3dB cutoff at 0.6Hz
FUZE HOLDER
Data Logging with ATmega 328p
External Connectors
I have no clue how this port should be wired.
So maybe use a CSTCE8M00G55-R0
8MHz uses a smaller power draw
Internal osc. may cause problems
5V max with I = 1A
Max current is going to be 1A
Since we're fused for 1.25A
5V max with I = 1.25A
Ensure to include power loss of ALL components on this board!

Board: 2 copper layers, 24 parts (0 on the bottom side), 21 nets, no tracks yet.

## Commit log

2017-02-19 Initialization
    Files striaght from Gdrive
2017-02-28 Edited Readme to notify of future file purge
    Im going to purge this repo when I have time to start creating V4 of the
    board. I'll also include my personal eagle libraries into this repo.
    V4 is planned to use SMD MCUs, boost-buck circuitry, LCD, and has a
    stretch goal of including an 120VAC input option. V4 is going to make
    this board extremely utilitarian.
2017-03-04 A bunch of code updates (not tested)
    changed basically all the code. I'll have to test it once I get my hands
    on a 328p
2017-03-20 adaptor board for shells equipment
2017-04-01 Parts list without MCU
2017-05-03 purged code base and added a new 12V regulator
    Code is to be rewritten.
    12V regulator can now supports an input voltage less than 12V. For a
    range 6V-18V
    I need to add a +/- 12 or 15V charge pump for the op amps.
2017-05-03 Cleaning the V4.0 folder
2017-05-03 Changed the README
2017-05-11 V4.0 UPDATE
2017-05-14 End of work session commit
    Not complete*
2017-05-18 Add current sensor
    Still need new 5V regulator and a -12V source for the op amps
2017-05-19 Added -12V Source for OPAMPS
    Still need a new surface mount 5V 1A regulator.
    After that, ill do a schematic review and begin the layout for the
    board.
2017-05-20 Added new 5V surface mount regulator
    Gotta do design check, then start building the board
2017-05-25 Using nMOS reverse polarity protection
    -added a cheaper 10uH inductor to the 5V supply
2017-05-25 Minor folder clean up
    -moved gerbers into V3.4 along with V3.4's "list of parts" spreadsheet
2017-05-25 updated gitignore
    hopefully this will make it so github doesnt track the .lck files.
2017-05-25 remove synced lck file.
    apparently there's a lck file in the repo.
2017-05-27 New circuit protection
    -40V- 60V protection.
    LED indication for blown fuse and reverse polarity.
    operates 8V- 18V
2017-05-30 Minor Changes/tweaks
2017-05-30 Added Jumpers to enable/disable data-logging
    cheap solution to avoid wasting power
2017-05-30 Changed to a SOIC opamp
    Easier to solder. Had issues with the smaller opamps in the previous
    version.
    The op-amp i spec'ed out also has a small DC bias (1mV and uses 45uA to
    bias)
2017-05-31 Added EAGLE Libraries
2017-05-31 Added Sample Code
    Something I worked on for a proof of concept. It takes the voltage of a
    pin creates a historigram with it. It communicates via I2C with a 128x64
    OLED matrix display.
    Will be modified to read 2 pins and output the power use and other
    statistics if needed.
2017-05-31 Made some changes to protection
    Desided to make a crowbar for overvoltage instead.
2017-06-01 Made some tweaks
    Changed some values in the power protection circuit
2017-06-01 Bunch of tweaks to lower cost and posted the parts list
2017-06-01 Accidently saved as EAGLE 8.2
    EAGLE 8.2+ changed how it saves projects. I had to re-save for legacy
    support (I believe our members are using version 7.x)
2017-06-02 Changed Crowbar
    The top of the zener is attached before the fuse. That way if the SCR is
    triggered due to over voltage, the fault LEDs will stay illuminated.
2017-06-02 Saved 1.75$
    Changed a few capacitors to save some money
2017-06-02 when git fails to sync
2017-06-02 Trying this commit again
2017-06-02 ignore schematic and board backups
2017-06-04 Added 10k pulldown on SCR
2017-07-19 Made some updates, generated BRD file
    -Used a 10k bridging resistor at battery input
    -forgot to fully connected the SCR to the negative terminal (fixed it)
    -Generated board file. Maximum demention for board is 10cmX10cm. May
    have to utlize the other side of the board to make it smaller.
2017-07-20 Increased pad length of current sensor
2017-09-07 Generated the board file
    -Generated Board files
    -Sorted the components
2017-09-11 Worked on PCB (Input)
    -Not complete
2018-01-09 Deleted -12V REG and op-amps
    They add complexity/expense/risk without adding much performance.
    When testing the -12V on the motor controller, the performance was poor. I am too lazy to re-spec a part so its much more efficient on time to just remove it.
2018-04-19 Added Most recent version
2018-05-26 Started a new aux power board
    Made significant changes to aux power. Also added components for the horn
2018-06-09 Made changes to aux power board, created horn board
2018-06-10 Horn Board almost 100%
    Finished horn board, just need to review. Made a few changes to the aux power board, still a work in progress
2018-06-15 More changes
